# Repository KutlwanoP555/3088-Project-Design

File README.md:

**** Repository for a power subsystem****

Group 127 
EEE3088F Design principles

# ⚡ Micro-Mouse Power Subsystem

This repository documents the design of a  **Power Subsystem** for the Micro-Mouse (MM) project. The power subsystem is responsible for delivering regulated power to all components of the micro-mouse.
---

## 📋 System Requirements

To meet the course requirements, the power subsystem must achieve the following:

- ✅ **Drive up to 4 motors bidirectionally**, using the assigned pins.
  - 2x brushed DC motors (200 mA each)
  - 2x auxiliary motors (500 mA each)
- ✅ **Integrate an INA219** for battery monitoring via I²C.
  - A0 and A1 pins must not both be tied to GND.
- ✅ **Charge the battery from a 9V input source.**
- ✅ **Support two charging modes**:
  - Low current: 200 mA
  - High current: 600 mA ±100 mA (from the battery's perspective)
- ✅ **Integrate USB-C** and negotiate a **9V supply** from a USB host.
- ✅ **Provide 2x external load switches**:
  - Must support 1 A each, with high-side connection to 5V.
- ✅ **Provide regulated 3.3V and 5V outputs**:
  - 3.3V @ 300 mA max ±5% accuracy
  - 5V @ 1.5 A max ±5% accuracy
- ✅ **Include an ON/OFF switch**:
  - OFF: Leakage current < 30 μA
  - ON: Must handle up to 2 A peak current
  - Must shut down both 5V and 3.3V rails

---

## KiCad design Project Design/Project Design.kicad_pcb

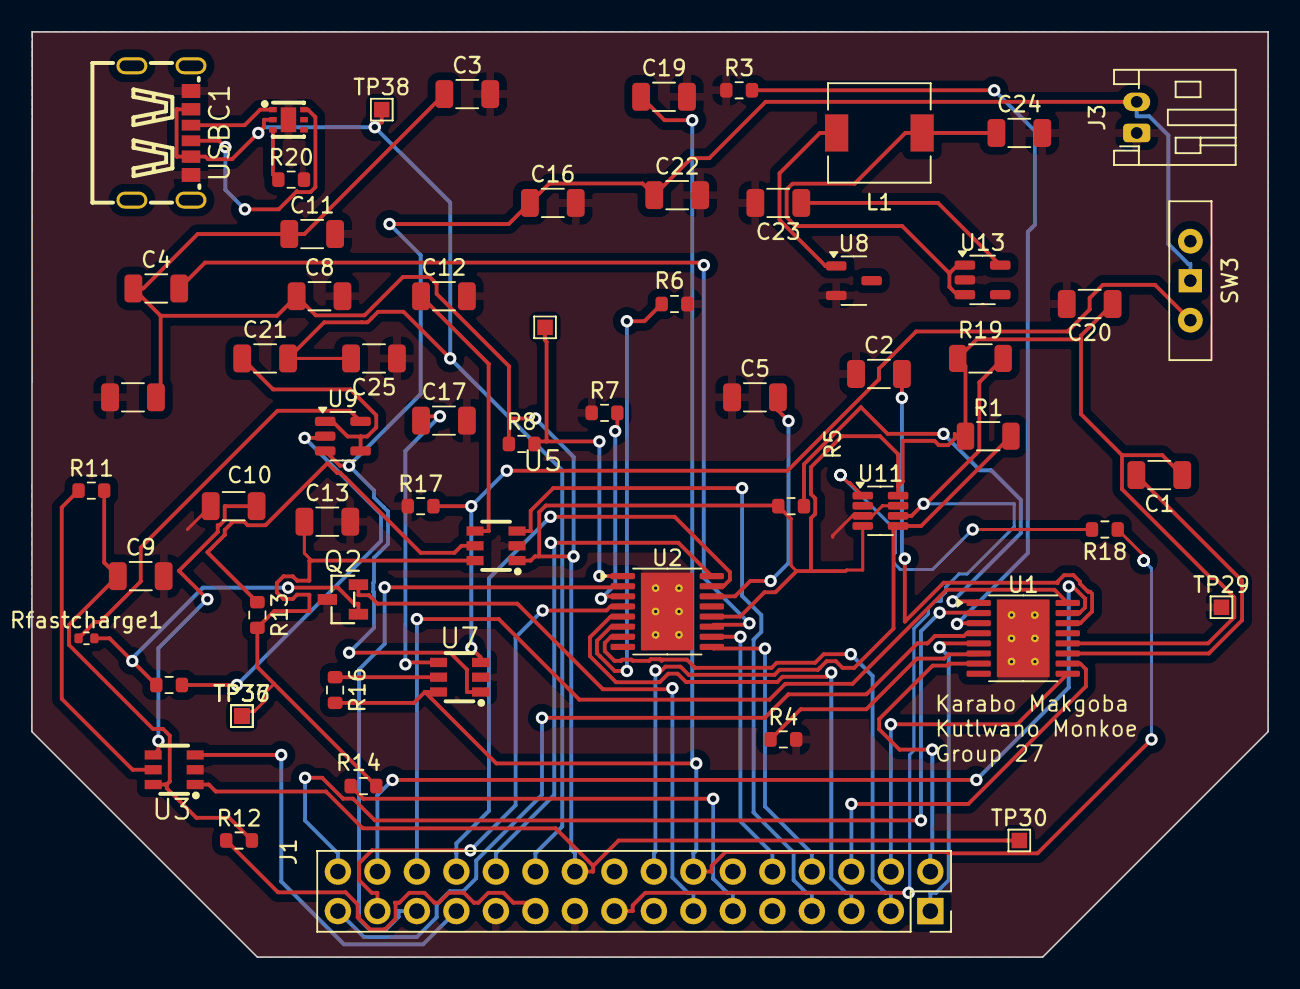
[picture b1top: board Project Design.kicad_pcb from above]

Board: 2 copper layers, 79.5 x 59.5 mm, 61 parts (0 on the bottom side), 58 nets.

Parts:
C1, C4: 0.01uF; C_1206_3216Metric
C2, C5: 2.2uF; C_1206_3216Metric
C3, C6, C9, C13, C19: 10uF; C_1206_3216Metric
C8, C10, C11, C12, C16, C17, C23, C24, C25: 1uF; C_1206_3216Metric
C20: 22uF; C_1206_3216Metric
C21, C22: 4.7uF; C_1206_3216Metric
J1: Conn_02x16_Odd_Even; PinHeader_2x16_P2.54mm_Vertical
J3: Conn_01x02_Pin; JST_PH_S2B-PH-K_1x02_P2.00mm_Horizontal
L1: 4.7uH; L_6.3x6.3_H3
Q2: NMOS; SOT-23-3_L2.9-W1.3-P1.90-LS2.4-BR
R1, R19: 1k; R_1206_3216Metric
R3, R4: 1R; R_0603_1608Metric
R5, R8: 47K; R_0603_1608Metric
R6, R7: 0.4R; R_0603_1608Metric
R11, R13, R16: 62R; R_0603_1608Metric
R12, R14: 5R2; R_0603_1608Metric
R17: 10k; R_0603_1608Metric
R18: 0.001; R_0603_1608Metric
R20: 75R; R_0603_1608Metric
R_normalcharging1: 3K; R_0603_1608Metric
Rfastcharge1: 2K; R_0402_1005Metric
SW3: SW_Wuerth_450301014042; SW_Slide-03_Wuerth-WS-SLTV_10x2.5x6.4_P2.54mm
TP26, TP29, TP30, TP36, TP37, TP38: TestPoint_Small; TestPoint_Pad_1.0x1.0mm
U1, U2: DRV8833PWP; HTSSOP-16-1EP_4.4x5mm_P0.65mm_EP3.4x5mm_Mask2.46x2.31mm_The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
U3, U5, U7: TPS22918TDBVRQ1; SOT-23-6_L2.9-W1.6-P0.95-LS2.8-BR
U8: TPS613222ADBV; SOT-23-3
U9: MCP73812T-420I-OT; SOT-23-5
U10: HUSB237-AA001-DN06R; TDFN-6_L2.0-W2.0-P0.65-TL-EP
U11: INA219AIDCNR; SOT-23-8
U13: AP2112K-3.3; TSOT-23-5
USBC1: USB 3.1 C 6PF; USB-C-SMD_TYPE-C-USB-13

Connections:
/5V: C1.1, C3.1, C4.1, C6.2, C8.1, C11.1, C20.1, J1.20, R1.1, R5.1, R8.1, R19.1, TP30.1, U1.12 (VM), U2.12 (VM), U3.1 (VIN), U5.1 (VIN), U11.4 (VS), U11.8 (A1)
/9V: C21.2, C25.2, J1.22, TP38.1, U10.2 (VUSB), USBC1.A9 (VBUS), USBC1.B9 (VBUS)
/Fast charge CTR: J1.13, Q2.2 (G)
/I2C1_SCL: J1.16, R1.2, U11.5 (SCL)
/I2C1_SDA: J1.17, R19.2, U11.6 (SDA)
/Mtr1 C1: J1.28, U1.16 (AIN1)
/Mtr1 C2: J1.30, U1.15 (AIN2)
/Mtr1 O1: J1.32, U1.2 (AOUT1)
/Mtr1 O2: J1.31, U1.4 (AOUT2)
/Mtr2 C1: J1.4, U1.9 (BIN1)
/Mtr2 C2: J1.6, U1.10 (BIN2)
/Mtr2 O1: J1.2, U1.7 (BOUT1)
/Mtr2 O2: J1.1, U1.5 (BOUT2)
/Mtr3 C1: J1.24, U2.16 (AIN1)
/Mtr3 C2: J1.26, U2.15 (AIN2)
/Mtr3 O1: J1.27, U2.2 (AOUT1)
/Mtr3 O2: J1.29, U2.4 (AOUT2)
/Mtr4 C1: J1.8, U2.9 (BIN1)
/Mtr4 C2: J1.10, U2.10 (BIN2)
/Mtr4 O1: J1.3, U2.7 (BOUT1)
/Mtr4 O2: J1.5, U2.5 (BOUT2)
/V+: C19.1, J1.14, R16.2, R18.1, U7.6 (VOUT)
/Vbat+: C16.1, C22.1, J3.2, SW3.1 (B), U7.1 (VIN), U9.3 (V_{BAT})
/Vload: C24.1, L1.1, U13.1 (VIN), U13.3 (EN)
/ex ctrl1: J1.25, U3.3 (ON)
/ex ctrl2: J1.7, U5.3 (ON)
/out1: J1.21, R12.1
/out2: J1.11, R14.1
GND: C2.1, C3.2, C5.1, C6.1, C8.2, C9.2, C10.2, C11.2, C12.2, C13.2, C16.2, C17.2, C19.2, C20.2, C22.2, C23.2, C24.2, C25.1, J1.19, J1.23, J3.1, Q2.3 (S), R3.1, R4.2, R6.2, R7.1, R17.1, R20.2, TP29.1, U1.13 (GND), U1.17 (GND(PPAD)), U2.13 (GND), U2.17 (GND(PPAD)), U3.2 (GND), U5.2 (GND), U7.2 (GND), U8.2 (GND), U10.7 (GND), U11.3 (GND), U11.7 (A0), U13.2 (GND), USBC1.A12 (GND), USBC1.B12 (GND)
unnamed: Q2.1 (D), R_normalcharging1.1, Rfastcharge1.2
unnamed: R17.2, SW3.3 (A), U7.3 (ON)
unnamed: R3.2, U1.3 (AISEN)
unnamed: R4.1, U1.6 (BISEN)
unnamed: C1.2, U1.11 (VCP)
unnamed: C2.2, U1.14 (VINT)
unnamed: R5.2, U1.1 (nSLEEP)
unnamed: R7.2, U2.3 (AISEN)
unnamed: R6.1, U2.6 (BISEN)
unnamed: C4.2, U2.11 (VCP)
unnamed: C5.2, U2.14 (VINT)
unnamed: R8.2, TP26.1, U2.1 (nSLEEP)
unnamed: C10.1, U3.4 (CT)
unnamed: R11.1, U3.5 (QOD)
unnamed: C9.1, R11.2, R12.2, TP36.1, U3.6 (VOUT)
unnamed: C12.1, U5.4 (CT)
unnamed: R13.1, U5.5 (QOD)
unnamed: C13.1, R13.2, R14.2, TP37.1, U5.6 (VOUT)
unnamed: C17.1, U7.4 (CT)
unnamed: R16.1, U7.5 (QOD)
unnamed: L1.2, U8.1 (SW)
unnamed: C21.1, U9.1 (CE), U9.4 (V_{DD})
unnamed: Rfastcharge1.1, U9.5 (PROG)
unnamed: R_normalcharging1.2, U9.2 (V_{SS})
unnamed: U10.1 (CC1), USBC1.A5 (CC1)
unnamed: U10.6 (CC2), USBC1.B5 (CC2)
unnamed: R20.1, U10.3 (VSET)
unnamed: R18.2, U11.1 (IN+)
unnamed: C23.1, U13.5 (VOUT)

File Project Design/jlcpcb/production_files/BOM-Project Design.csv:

Comment,Designator,Footprint,LCSC,Quantity
4.7uH,L1,L_6.3x6.3_H3,C1034,1
10uF,"C13,C19,C6,C9",C_1206_3216Metric,C13585,4
MCP73812T-420I-OT,U9,SOT-23-5,C144308,1
DRV8833PWP,"U1,U2",HTSSOP-16-1EP_4.4x5mm_P0.65mm_EP3.4x5mm_Mask2.46x2.31mm_ThermalVias,C1556089,2
USB 3.1 C 6PF,USBC1,USB-C-SMD_TYPE-C-USB-13,C168701,1
0.4R,"R6,R7",R_0603_1608Metric,C171375,2
Conn_01x02_Pin,,JST_PH_S2B-PH-K_1x02_P2.00mm_Horizontal,C173752,0
10k,R17,R_0603_1608Metric,C17414,1
47K,"R5,R8",R_0603_1608Metric,C17713,2
5R2,"R12,R14",R_0603_1608Metric,C17724,2
1R,"R3,R4",R_0603_1608Metric,C17928,2
0.01uF,"C1,C4",C_1206_3216Metric,C1846,2
1uF,"C10,C11,C12,C16,C17,C20,C23,C24,C25,C3,C8",C_1206_3216Metric,C1848,11
TPS613222ADBV,U8,SOT-23-3,C2071163,1
NMOS,Q2,SOT-23-3_L2.9-W1.3-P1.90-LS2.4-BR,C20917,1
HUSB237-AA001-DN06R,U10,TDFN-6_L2.0-W2.0-P0.65-TL-EP,C22373734,1
TPS22918TDBVRQ1,"U3,U5,U7",SOT-23-6_L2.9-W1.6-P0.95-LS2.8-BR,C2653760,3
SW_Wuerth_450301014042,SW3,SW_Slide-03_Wuerth-WS-SLTV_10x2.5x6.4_P2.54mm,C2887259,1
4.7uF,"C21,C22",C_1206_3216Metric,C29823,2
2K,Rfastcharge1,R_0402_1005Metric,C4109,1
3K,R_normalcharging1,R_0603_1608Metric,C4211,1
75R,R20,R_0603_1608Metric,C4275,1
1k,"R1,R19",R_1206_3216Metric,C4410,2
62R,"R11,R13,R16",R_0603_1608Metric,C4962,3
0.001,R18,R_0603_1608Metric,C500734,1
2.2uF,"C2,C5",C_1206_3216Metric,C50254,2
AP2112K-3.3,U13,TSOT-23-5,C51118,1
INA219AIDCNR,U11,SOT-23-8,C87469,1
TestPoint_Small,TP38,TestPoint_Pad_1.0x1.0mm,,1
TestPoint_Small,TP37,TestPoint_Pad_1.0x1.0mm,,1
TestPoint_Small,TP36,TestPoint_Pad_1.0x1.0mm,,1
TestPoint_Small,TP30,TestPoint_Pad_1.0x1.0mm,,1
TestPoint_Small,TP29,TestPoint_Pad_1.0x1.0mm,,1
TestPoint_Small,TP26,TestPoint_Pad_1.0x1.0mm,,1
Conn_02x16_Odd_Even,,PinHeader_2x16_P2.54mm_Vertical,,0

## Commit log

2025-03-20 Adding project files to github
2025-03-23 Added the two Amp circuit and still wanna work on the motor driver
2025-03-23 Updated my part
2025-03-24 Fixed motor set up also added components that we will need for the USB C 9V charging
2025-03-25 Add to the usb section still need to update it, add footprint for the 6P connector. I might opt for a 16P connector which is honestly overkill in my opinion
2025-03-26 Thing are neat
2025-03-26 Putting everything together
2025-03-28 updated part numbers
2025-04-08 Final design, hopefully it works
